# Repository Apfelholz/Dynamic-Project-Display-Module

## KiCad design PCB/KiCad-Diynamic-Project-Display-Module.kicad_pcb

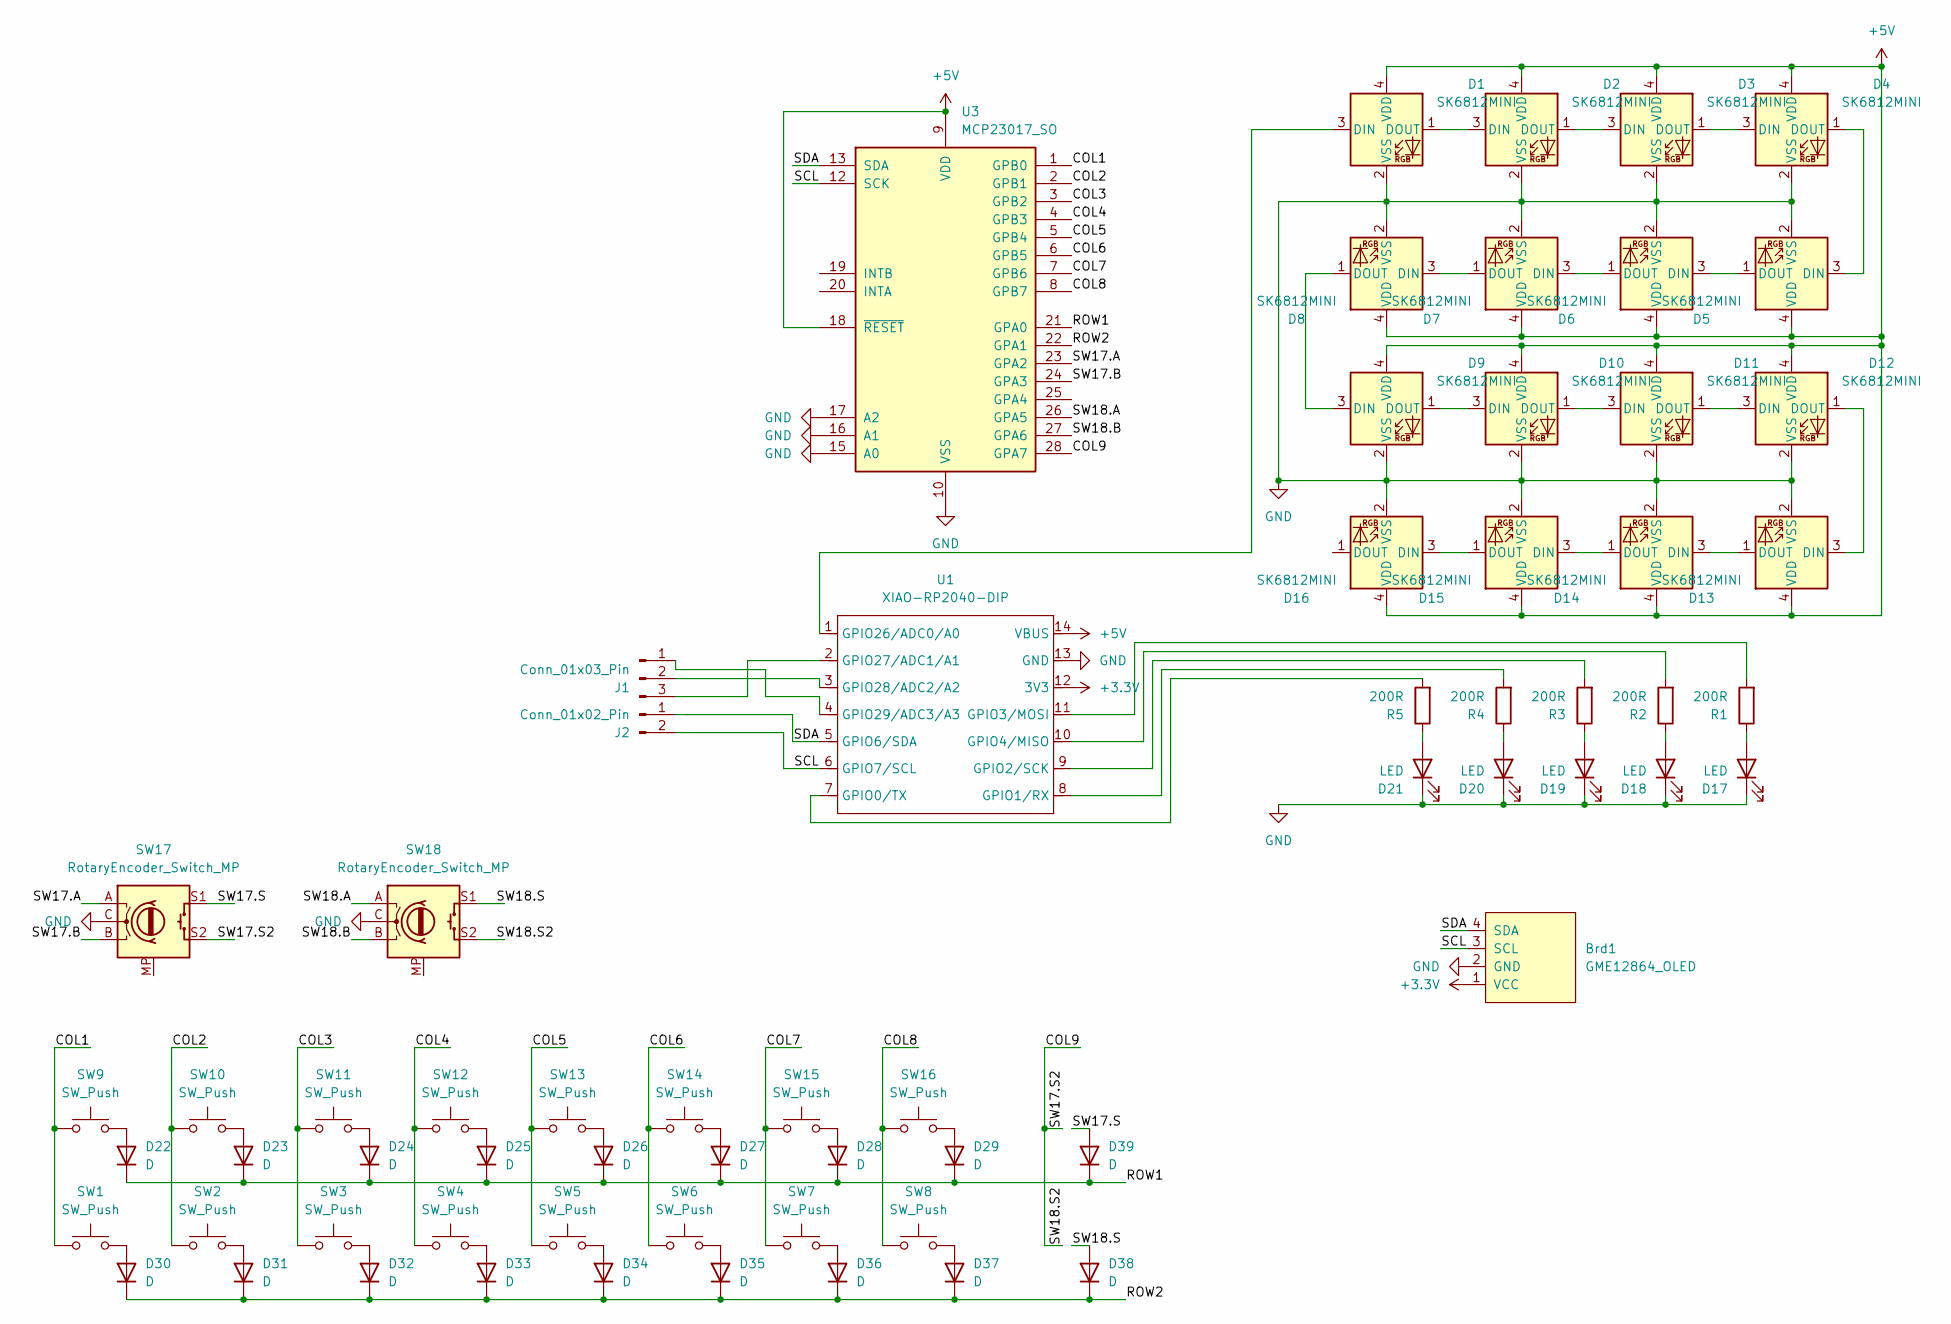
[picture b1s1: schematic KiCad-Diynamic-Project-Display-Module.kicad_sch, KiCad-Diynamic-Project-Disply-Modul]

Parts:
Brd1: GME12864_OLED; SSD1306-0.91-OLED-4pin-128x32
D1, D2, D3, D4, D5, D6, D7, D8, D9, D10, D11, D12, D13, D14, D15, D16: SK6812MINI; LED_SK6812MINI_PLCC4_3.5x3.5mm_P1.75mm
D17, D18, D19, D20, D21: LED; LED_D5.0mm
D22, D23, D24, D25, D26, D27, D28, D29, D30, D31, D32, D33, D34, D35, D36, D37, D38, D39: D; D_SOD-123
J1: Conn_01x03_Pin; PinHeader_1x03_P2.54mm_Horizontal
J2: Conn_01x02_Pin; PinHeader_1x02_P2.54mm_Horizontal
R1, R2, R3, R4, R5: 200R; R_0805_2012Metric_Pad1.20x1.40mm_HandSolder
SW1, SW2, SW3, SW4, SW5, SW6, SW7, SW8, SW9, SW10, SW11, SW12, SW13, SW14, SW15, SW16: SW_Push; SW_Cherry_MX_1.00u_PCB
SW17, SW18: RotaryEncoder_Switch_MP; RotaryEncoder_Alps_EC11E-Switch_Vertical_H20mm_MountingHoles
U1: XIAO-RP2040-DIP
U3: MCP23017_SO; SOIC-28W_7.5x17.9mm_P1.27mm

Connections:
+3.3V: Brd1.1 (VCC), U1.12 (3V3)
+5V: D1.4 (VDD), D2.4 (VDD), D3.4 (VDD), D4.4 (VDD), D5.4 (VDD), D6.4 (VDD), D7.4 (VDD), D8.4 (VDD), D9.4 (VDD), D10.4 (VDD), D11.4 (VDD), D12.4 (VDD), D13.4 (VDD), D14.4 (VDD), D15.4 (VDD), D16.4 (VDD), U1.14 (VBUS), U3.9 (VDD), U3.18 (~RESET)
/COL1: SW1.1, SW9.1, U3.1 (GPB0)
/COL2: SW2.1, SW10.1, U3.2 (GPB1)
/COL3: SW3.1, SW11.1, U3.3 (GPB2)
/COL4: SW4.1, SW12.1, U3.4 (GPB3)
/COL5: SW5.1, SW13.1, U3.5 (GPB4)
/COL6: SW6.1, SW14.1, U3.6 (GPB5)
/COL7: SW7.1, SW15.1, U3.7 (GPB6)
/COL8: SW8.1, SW16.1, U3.8 (GPB7)
/COL9: SW17.S2, SW18.S2, U3.28 (GPA7)
/ROW1: D22.1 (K), D23.1 (K), D24.1 (K), D25.1 (K), D26.1 (K), D27.1 (K), D28.1 (K), D29.1 (K), D39.1 (K), U3.21 (GPA0)
/ROW2: D30.1 (K), D31.1 (K), D32.1 (K), D33.1 (K), D34.1 (K), D35.1 (K), D36.1 (K), D37.1 (K), D38.1 (K), U3.22 (GPA1)
/SCL: Brd1.3 (SCL), J2.2, U1.6 (GPIO7/SCL), U3.12 (SCK)
/SDA: Brd1.4 (SDA), J2.1, U1.5 (GPIO6/SDA), U3.13 (SDA)
/SW17.A: SW17.A, U3.23 (GPA2)
/SW17.B: SW17.B, U3.24 (GPA3)
/SW17.S: D39.2 (A), SW17.S1
/SW18.A: SW18.A, U3.26 (GPA5)
/SW18.B: SW18.B, U3.27 (GPA6)
/SW18.S: D38.2 (A), SW18.S1
GND: Brd1.2 (GND), D1.2 (VSS), D2.2 (VSS), D3.2 (VSS), D4.2 (VSS), D5.2 (VSS), D6.2 (VSS), D7.2 (VSS), D8.2 (VSS), D9.2 (VSS), D10.2 (VSS), D11.2 (VSS), D12.2 (VSS), D13.2 (VSS), D14.2 (VSS), D15.2 (VSS), D16.2 (VSS), D17.1 (K), D18.1 (K), D19.1 (K), D20.1 (K), D21.1 (K), SW17.C, SW18.C, U1.13 (GND), U3.10 (VSS), U3.15 (A0), U3.16 (A1), U3.17 (A2)
unnamed: D1.3 (DIN), U1.1 (GPIO26/ADC0/A0)
unnamed: D1.1 (DOUT), D2.3 (DIN)
unnamed: D2.1 (DOUT), D3.3 (DIN)
unnamed: D3.1 (DOUT), D4.3 (DIN)
unnamed: D4.1 (DOUT), D5.3 (DIN)
unnamed: D5.1 (DOUT), D6.3 (DIN)
unnamed: D6.1 (DOUT), D7.3 (DIN)
unnamed: D7.1 (DOUT), D8.3 (DIN)
unnamed: D8.1 (DOUT), D9.3 (DIN)
unnamed: D9.1 (DOUT), D10.3 (DIN)
unnamed: D10.1 (DOUT), D11.3 (DIN)
unnamed: D11.1 (DOUT), D12.3 (DIN)
unnamed: D12.1 (DOUT), D13.3 (DIN)
unnamed: D13.1 (DOUT), D14.3 (DIN)
unnamed: D14.1 (DOUT), D15.3 (DIN)
unnamed: D15.1 (DOUT), D16.3 (DIN)
unnamed: D17.2 (A), R1.1
unnamed: D18.2 (A), R2.1
unnamed: D19.2 (A), R3.1
unnamed: D20.2 (A), R4.1
unnamed: D21.2 (A), R5.1
unnamed: D22.2 (A), SW9.2
unnamed: D23.2 (A), SW10.2
unnamed: D24.2 (A), SW11.2
unnamed: D25.2 (A), SW12.2
unnamed: D26.2 (A), SW13.2
unnamed: D27.2 (A), SW14.2
unnamed: D28.2 (A), SW15.2
unnamed: D29.2 (A), SW16.2
unnamed: D30.2 (A), SW1.2
unnamed: D31.2 (A), SW2.2
unnamed: D32.2 (A), SW3.2
unnamed: D33.2 (A), SW4.2
unnamed: D34.2 (A), SW5.2
unnamed: D35.2 (A), SW6.2
unnamed: D36.2 (A), SW7.2
unnamed: D37.2 (A), SW8.2
unnamed: J1.1, U1.4 (GPIO29/ADC3/A3)
unnamed: J1.2, U1.3 (GPIO28/ADC2/A2)
unnamed: J1.3, U1.2 (GPIO27/ADC1/A1)
unnamed: R5.2, U1.7 (GPIO0/TX)
unnamed: R4.2, U1.8 (GPIO1/RX)
unnamed: R3.2, U1.9 (GPIO2/SCK)
unnamed: R1.2, U1.11 (GPIO3/MOSI)
unnamed: R2.2, U1.10 (GPIO4/MISO)

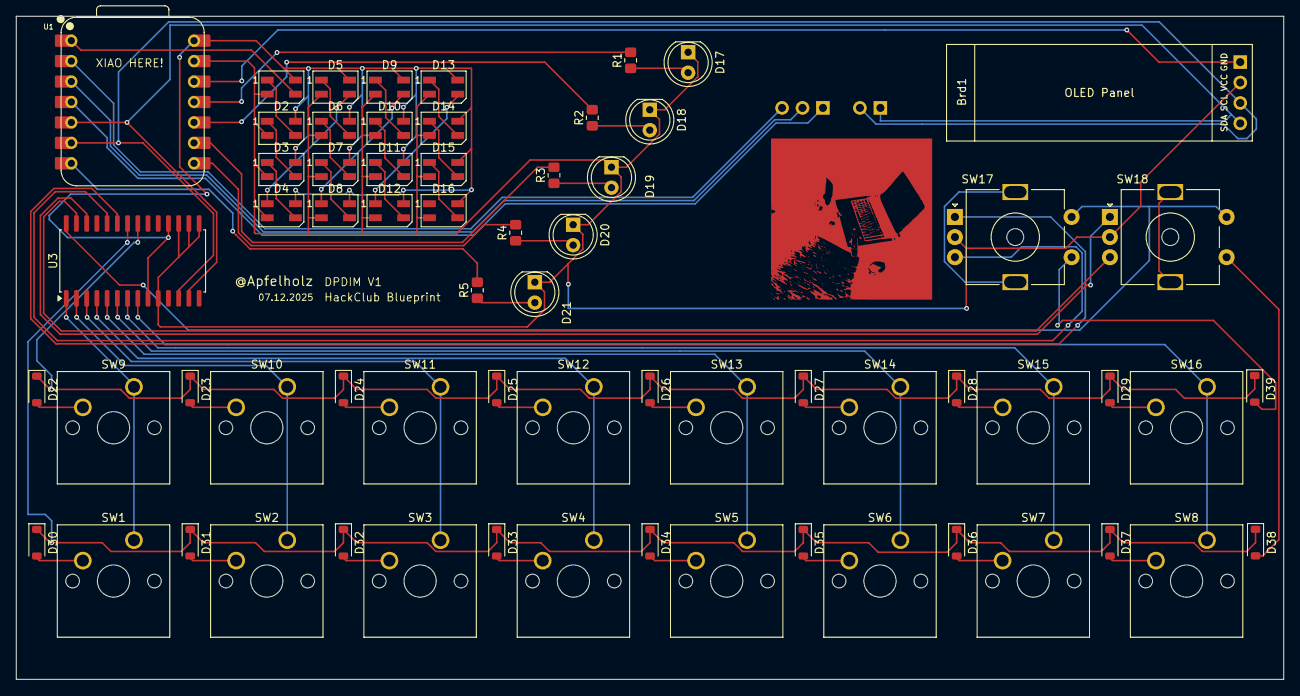
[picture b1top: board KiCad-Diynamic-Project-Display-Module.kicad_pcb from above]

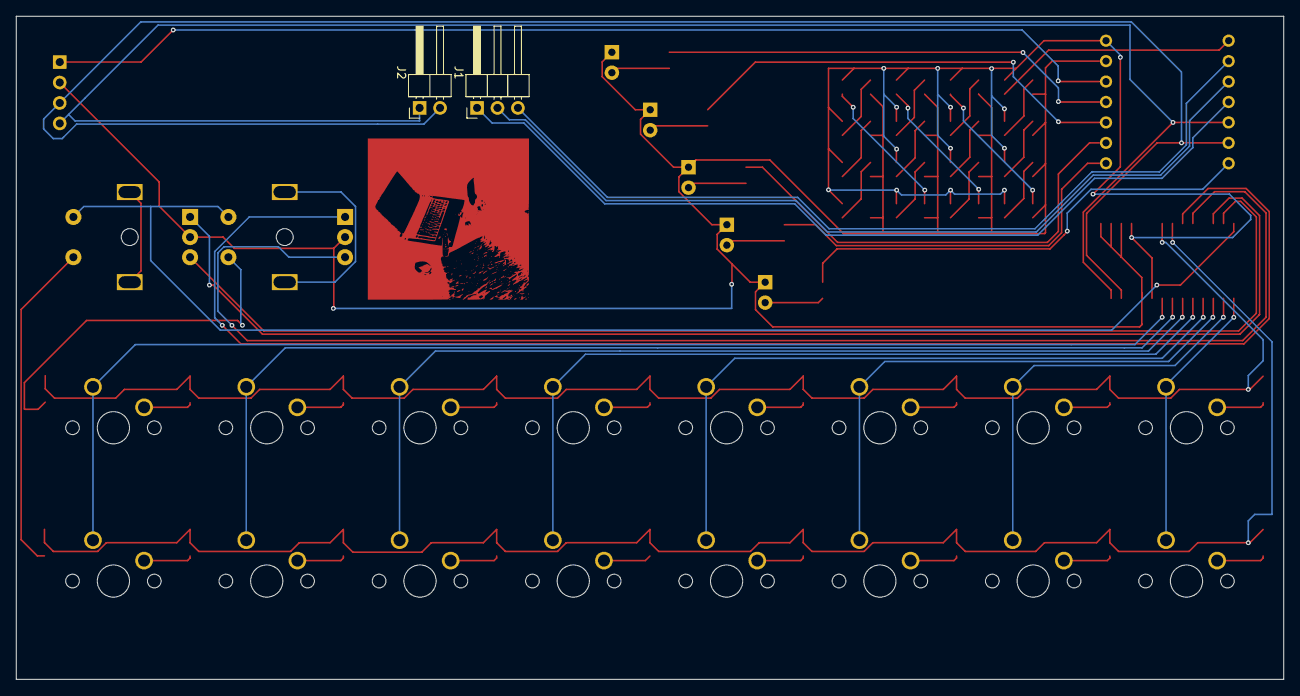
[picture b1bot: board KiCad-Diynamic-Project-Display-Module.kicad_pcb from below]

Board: 2 copper layers, 157.5 x 82.4 mm, 67 parts (2 on the bottom side), 67 nets.

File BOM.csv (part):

KICad BOM,                                                                          ,                                                             ,          ,                        ,                                                                                                                                                                                                                                                                                                                                                                                                                                                                                                                                                                                                                                                                                                                                                                                                                                                                                                                     ,               , 
ID       , Bezeichner                                                               , Footprint                                                   , Stückzahl, Bezeichnung            , Link                                                                                                                                                                                                                                                                                                                                                                                                                                                                                                                                                                                                                                                                                                                                                                                                                                                                                                                , Unit Price (€), Total Price (€)
1        , "R5,R3,R4,R1,R2"                                                         , R_0805_2012Metric_Pad1.20x1.40mm_HandSolder                 , 5        , 200R                   , https://de.aliexpress.com/item/1005003413960273.html?spm=a2g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                                                                                                                                                                 , -             , "4,04"
2        , "SW3,SW6,SW2,SW16,SW10,SW14,SW12,SW8,SW7,SW5,SW13,SW9,SW4,SW11,SW1,SW15" , SW_Cherry_MX_1.00u_PCB                                      , 16       , SW_Push                , https://www.reichelt.de/de/de/shop/produkt/cherry_mx_blue_-_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                                                                                                                                                                                                                                                                                                                                                                                                                                                                                                                                                                                                                                                                                                                                                                                                                       , "0,45"        , "7,2"
3        , "D37,D24,D34,D28,D31,D22,D23,D32,D30,D27,D39,D33,D35,D29,D26,D36,D25,D38", D_SOD-123                                                   , 18       , D                      , https://de.aliexpress.com/item/1005007118972345.html?spm=a2g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                                                                                                                                                                                                                                                                                    , -             , "3,64"
4        , "D9,D12,D1,D13,D2,D14,D8,D16,D3,D11,D15,D5,D7,D4,D10,D6"                 , LED_SK6812MINI_PLCC4_3.5x3.5mm_P1.75mm                      , 16       , SK6812MINI             , https://de.aliexpress.com/item/1005007863635868.html?spm=a2g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                                                                                                                                                                                                                                                        , -             , "3,44"
5        , "D21,D18,D19,D20,D17"                                                    , LED_D5.0mm                                                  , 5        , LED                    , "https://de.aliexpress.com/item/1005005708510866.html?spm=a2g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,scm-url:1007.40050.354490.0,pvid:0cdca9ac-4e5f-4922-92b4-0dfb00177358,tpp_buckets:668%232846%238110%231995&pdp_ext_f=%7B%22order%22%3A%224816%22%2C%22eval%22%3A%221%22%2C%22sceneId%22%3A%2230050%22%2C%22fromPage%22%3A%22recommend%22%7D&pdp_npi=6%40dis%21EUR%211.28%210.99%21%21%2110.35%218.01%21%40211b629217656668978617450e697a%2112000034078716878%21rec%21DE%21%21ABXZ%211%210%21n_tag%3A-29910%3Bd%3A883e50a7%3Bm03_new_user%3A-29895%3BpisId%3A5000000187464813&utparam-url=scene%3ApcDetailTopMoreOtherSeller%7Cquery_from%3A%7Cx_object_id%3A1005005708510866%7C_p_origin_prod%3A", -             , "1,69"
6        , Brd1                                                                     , SSD1306-0.91-OLED-4pin-128x32                               , 1        , GME12864_OLED          , https://de.aliexpress.com/item/1005008640108394.html?spm=a2g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                                                                                                                                                                                                                                                        , 1             , "1,75"
7        , U1                                                                       , XIAO-RP2040-DIP                                             , 1        , XIAO-RP2040-DIP        , https://de.aliexpress.com/item/1005003683887126.html?spm=a2g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                                                                                                                                                                                                                                                                                    , 1             , "6,39"
8        , "SW17,SW18"                                                              , RotaryEncoder_Alps_EC11E-Switch_Vertical_H20mm_MountingHoles, 2        , RotaryEncoder_Switch_MP, https://de.aliexpress.com/item/1005008583446552.html?spm=a2g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                                                                                                                                                                                                                                                        , -             , "3,97"
9        , U3                                                                       , SOIC-28W_7.5x17.9mm_P1.27mm                                 , 1        , MCP23017_SO            , https://de.aliexpress.com/item/1005009034247985.html?spm=a2g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                                                                                                                                                                                                                                                                                    , -             , "3,99"
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
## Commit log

2025-12-05 the start of the scamatic
2025-12-13 Prodjekt
2025-12-14 Add Tap Dance functionality and various scanner implementations
    - Introduced TapDanceKey and TapDance classes for enhanced key press handling.
    - Implemented MatrixScanner and RotaryioEncoder for key matrix and rotary encoder support.
    - Added KeypadScanner and its subclasses for different keypad configurations.
    - Created PIO_UART class for UART communication using PIO.
    - Added utility functions and debugging support in utils.py.
    - Established a main.py file to initialize the keyboard with I2C, matrix, RGB, OLED, and encoder support.
2025-12-14 Enhance JsonAPI with error handling and additional commands for OLED and encoder interactions
2025-12-14 Refactor JsonAPI's on_key_event method for improved readability
2025-12-14 Refactor code structure for improved readability and maintainability
2025-12-14 change folder struckture to match recuerments
2025-12-14 Refactor BOM.csv format for improved readability and consistency; add detailed project journal in JOURNAL.md; update README.md with new content.
2025-12-15 Refactor BOM.csv for improved formatting and readability; update component details and links.
2025-12-15 Update BOM.csv to include DSA keycaps and adjust total formatting for clarity
2025-12-16 add image of the shipping option and oubdate bom
